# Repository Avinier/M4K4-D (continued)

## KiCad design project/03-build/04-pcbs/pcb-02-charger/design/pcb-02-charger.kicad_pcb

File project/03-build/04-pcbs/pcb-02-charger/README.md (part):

# PCB-02 — Charger, latch and pack sense

> **Superseded by [D-093](../../decisions.md#d-093) (2026-11-06).** Replaced by bought modules: a pushbutton power switch and an INA226/219 voltage/current monitor. The pack is charged outside the robot, so there is no charger. The routed layout below is archived as reference for a later in-robot charger. Nothing here is built or ordered; the folder is kept as the record.

BQ25798 2S charger, on/off latch, pack sense, `ENERGY_OK` and the power-button input `J2-9`.

| | |
|---|---|
| Register | [04-pcbs board register](../README.md#board-register) |
| Project BOM | CH-041 in [BOM.csv](../../BOM.csv) |
| Location | Body, behind the rear panel (vertical) |
| Specification | [charge-path.md §4](../charge-path.md#4-pcb-02--charger-block)<br>[power-boards.md §6](../power-boards.md#6-pcb-02-power-button-input-d-041)<br>[RP-02 board-specs.md](../../../02-prototypes/RP-02-electrical/board-specs.md) (read-only reference)<br>[open items](../open-items.md) CP-OI-02, CP-OI-09, CP-OI-15<br>[D-040](../../decisions.md#d-040), [D-041](../../decisions.md#d-041) |
| CAD placeholder | `power_distribution_boards()` in [`body_v1_model.py`](../../02-body/v1/cad/body_v1_model.py) |
| CAD labels | `PCB02_CHARGE_AND_SYSTEM_POWER` |
| Final CAD | `Custom PCBs › PCB-02 charger, latch and pack sense` in [makad-v1.step.py](../../final/v1/cad/makad-v1.step.py) |

## Stages

See [workflow.md](../workflow.md) for what each stage involves and when it is done.

| Stage | Status | Revision / evidence | Date |
|---|---|---|---|
| 1. Design | In progress | Inputs frozen, frame mount checked (D-083); schematic ERC 0/0; fit-study placement of all 119 footprints at 50 × 36 mm (D-084); routing not started | 2026-11-03 |
| 2. Procure | — | — | — |
| 3. Integrate | — | — | — |

## Inputs

### Lesson 1 — input freeze (2026-11-02)

**Authority order.** The build baseline is [power-boards.md](../power-boards.md) (D-038), with charge-specific changes in [charge-path.md](../charge-path.md) and [D-040](../../decisions.md#d-040), followed by the button deltas in [D-041](../../decisions.md#d-041). The [RP-02 board specification](../../../02-prototypes/RP-02-electrical/board-specs.md) is read-only architecture history; where it differs, the build deltas win. The BOM identity is [CH-041](../../BOM.csv). The remaining gates are [CP-OI-02, CP-OI-06, CP-OI-09 and CP-OI-15](../open-items.md#charge-path-pcb-13-inlet-and-the-pcb-02-charger-d-040-charge-pathmd).

Primary-source cross-checks for this lesson: TI [BQ25798 Rev C datasheet](https://www.ti.com/lit/ds/slusdv2c/slusdv2c.pdf) and [BQ25798EVM user guide](https://www.ti.com/lit/ug/sluucb5c/sluucb5c.pdf); Würth [74437346022 datasheet](https://www.we-online.com/components/products/datasheet/74437346022.pdf). Sourcing pages checked: [LCSC BQ25798RQMR C2876593](https://www.lcsc.com/product-detail/C2876593.html), [element14 India LTC2954 order 4027758](https://in.element14.com/analog-devices/ltc2954its8-2-trpbf/pushbutton-controller-26-4v-tsot/dp/4027758), and [LCSC LTC2954 C580656](https://www.lcsc.com/product-image/C580656.html).

**Fixed electrical boundary.** PCB-13 rev A owns the USB-C receptacle, PD negotiation and input switch. PCB-02 receives only the switched `VSNK` and ground at `J2-8`; the connector pinout and voltage/current envelope below are fixed by [PCB-13's interface freeze](../pcb-13-charge-inlet/README.md#interface-to-pcb-02-fixed-here). `J2-9` is the side-entry GH2 power-button input required by D-041.

| PCB-02 connector / destination | Contract frozen for schematic |
|---|---|
| `J2-8` from PCB-13 | Micro-Fit 3.0 2-way, pin 1 `VSNK`, pin 2 `GND`; normal 9/15 V, blank-STUSB NVM 20 V, 28.35 V surge ceiling; 1.38 A normal maximum and 3 A design current. |
| `J2-1` to pack/fuse-side star | Micro-Fit+ 1×2, pin 1 `BATBUS-C`, pin 2 `PGND` (star). `J2-2` is deleted by D-039; the pack does not connect directly to PCB-02's charger `BAT` sense point. `BATP` returns by a separate 100 Ω Kelvin connection to pin 1. |
| `J2-3` to PCB-04 | Micro-Fit+ 2×2: pin 1 `OPBUS`, pin 2 `CHGBUS`, pin 3 `OPBUS_RTN`, pin 4 `CHGBUS_RTN`. The harness carries operating power and charge-only logic power separately. |
| `J2-4` to PCB-04 | GH10 pin order: 1 GND, 2 `+5V_C2`, 3 `PG_C2`, 4 `PG_BASE`, 5 `SEQ_EN`, 6 `PG_COMPUTE`, 7 `PG_DISPLAY`, 8 `PG_AUDIO`, 9 spare, 10 GND. |
| `J2-5` to PCB-03 | GH8 pin order (D-082): 1 GND, 2 `CHARGE_ABSENT`, 3 `ENERGY_OK`, 4 `SYSTEM_ARM`, 5 `MOTOR_PRESENT`, 6 GND, 7 `PERMIT_OK`, 8 GND. `ENERGY_OK` is active-high/open-drain with a PCB-02 pull-up to switched `+5V_C2`; PCB-03 adds a physical receiver pull-down so an open/unpowered source defaults to motor-inhibit. Pull-up/pull-down values must be co-checked against the receiver's VIH/VIL, leakage and cable margin before the schematic is released. |
| `J2-6` to C2/head sideband | GH8 pin order: 1 `SIG_GND`, 2 `V_PACK_ANA`, 3 `SIG_GND`, 4 `STAT`, 5 `INT_PB`, 6 `KILL`, 7 `CHG_ABSENT_3V3`, 8 `ARM_REQ` (D-082). |
| `J2-7` to pack NTC | GH2: both 103AT-2 leads return to PCB-02; one lead is `TS`, the other BQ25798 ground-pad return. Do not return through a cell or `B−` path behind the pack protector. |
| `J2-9` to rear power button | Side-entry JST GH2 (SM02B-GHS-TB), pin 1 `PB_SW`, pin 2 signal `GND`; plug exits +Y, centred Z 88.6. Board includes the 10 kΩ VIN-to-`PB_SW` wetting resistor, the 5.1 kΩ / 0.1 µF `PB` network, and `INT` resets `SYSTEM_ARM`. The button is the power latch input and hardware motor-stop request; there is no E-stop. |

These orders are a board contract, not a layout proposal. Carry the exact 05-harness pin maps into the schematic, preserve separation between `OPBUS` and `CHGBUS`, and name the grounds according to their power/logic roles.

### Lesson 2 — circuit, from first principles (2026-11-02)

A PCB power board is easier to reason about as separate energy paths with explicit gates. A node name is a contract: `BATBUS` is pack energy at the fuse-side star, `OPBUS` is pack energy after the user-controlled operating switch, `VSNK` is adapter energy after PCB-13 has negotiated and switched it, and `SYS` is the BQ25798's system output. They may sit at similar voltages, but they are not interchangeable nets.

```text
USB-C adapter → PCB-13 PD + input FET → VSNK → BQ25798 → BAT / BATP → fused pack entry
                                                    └→ SYS → adapter-enabled gate → CHGBUS → PCB-04
pack → fuse-side star → BATBUS → Q_OP (LTC2954 latch) → OPBUS → PCB-04
                                             └──────────────→ sense + ENERGY_OK
VSNK → charge-present hardware → CHARGE_ABSENT / Q_dis / Q_kill
J2-9 button → LTC2954 PB; LTC2954 INT → clear SYSTEM_ARM and request C2 shutdown
```

The BQ25798 has an internal battery-to-`SYS` path, so `SYS` can be live from the pack even when no adapter is attached. The charge-only gate keeps that battery-backed node from energizing `CHGBUS` in `OFF` or `OPERATE`. PCB-02 sends `OPBUS` and `CHGBUS` as separate power/return pairs to PCB-04; the destination's reverse-blocking source paths keep charge-only power from back-feeding `OPBUS`. This is what permits C2 and the display to run from the adapter during `CHARGE` while the robot's operating bus remains off.

The operating path is separate. The LTC2954 remembers the momentary button state and drives the gate of `Q_OP`, a P-channel FET from `BATBUS` to `OPBUS`. The series permit chain on PCB-03 decides whether motor energy may pass; PCB-02 supplies the independent `CHARGE_ABSENT`, `ENERGY_OK`, and `SYSTEM_ARM` terms. A valid adapter immediately withdraws the charge-absent term so motor permission opens. `Q_kill` pulls LTC2954 `KILL` low and commands `Q_OP` off promptly, including during a button press in `CHARGE`. The roughly 3 s `Q_dis` hard block is a redundant path still to be captured and tested; it is not a three-second permission to keep `OPBUS` live.

The charger is a third path. `VSNK` feeds the BQ25798's `VBUS` and, by strap, both `VAC` pins. The device's internal switching bridge and the external 2.2 µH inductor move energy into the `BAT`/`SYS` outputs. `PROG` sets 2S, 1 A and 750 kHz without firmware; `ILIM_HIZ` limits input draw; the cell NTC at `TS` gates charging by temperature. `BATP` is a separate high-impedance sense connection returned through 100 Ω to the same fuse-side pack-entry point as `BAT`, so charge current through the fuse, harness and protector does not appear as a false pack-voltage change.

| State | Charger / `SYS` | Operating path | Logic and motor result |
|---|---|---|---|
| `OFF` | BQ25798 remains in low-current battery-only mode; `SYS` may be battery-live | LTC2954 is off; `Q_OP` leaves `OPBUS` open | `Q_sys` is open, so no C2/display logic rail; PCB-03 permit chain is inactive |
| `OPERATE` | Charger remains autonomous; no adapter input | Button latch closes `Q_OP`; `OPBUS` feeds operating loads | Logic runs from `OPBUS`; motors still require every PCB-03 permit term |
| `CHARGE` | `VSNK` powers the BQ25798; gated `SYS` is sent on `CHGBUS` | Charge-present path withdraws `CHARGE_ABSENT`; `Q_kill` commands `Q_OP` off promptly; delayed `Q_dis` is the backup hard block | C2/display run for indication; a button press cannot latch `OPERATE`; motors are inhibited |

The button press has two time scales. In `OPERATE`, LTC2954 `INT` drops after about 32 ms, so hardware clears `SYSTEM_ARM` and removes motor permission without waiting for firmware. C2 starts its orderly shutdown only after the press stays low for 1 s. Holding about 5.2 s invokes the latch's hardware force-off if C2 is hung. `R_WET` raises pressed-contact current from the LTC2954's internal-pull-up 19 µA to about 0.84 mA; the open switch consumes no `R_WET` current when released. This is a power button with a safety-stop function; there is no E-stop in this build.

**Lesson 2 decisions.** The read-only RP-02 `board-specs.md` has two `SYS`-gate descriptions: §4.1 shows a gated P-FET plus Schottky OR with `OPBUS`, while §6.3 describes a `TPS22810` gate to the separate `C2B`/`DISB` inputs and PCB-04 reverse-blocking e-fuses. The fixed harness sends separate `OPBUS` and `CHGBUS` rails. Use separate `OPBUS` and adapter-gated `CHGBUS`, leaving source ORing at PCB-04 as §6.3 describes. Carry 5.7 V falling / 6.4 V rising as provisional `ENERGY_OK` values, with the EN-02/03 calculation and bench validation as release gates.

Second, the RP-02 board-spec proposal is 5.7 V falling (5.53–5.87 V), 6.4 V rising, 1 ms falling qualification and at least 100 ms clear dwell, sensed on loaded `OPBUS`. `power-boards.md` carries the 5.7 V value forward. But the registered [brownout/reset contract](../../../02-prototypes/RP-02-electrical/brownout-restart-contract.md) says numeric thresholds remain evidence-gated and lists the pack, converter, path-resistance, stop-load, monitor-accuracy and reaction-time inputs that must be bound before a threshold is valid. Therefore 5.7/6.4 V is a candidate circuit target, not a released safety setting. The comparator topology and exact IC are also open; the board spec calls only for a local C2-branch 3.3 V supply, nano-power comparator and open-drain output.

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
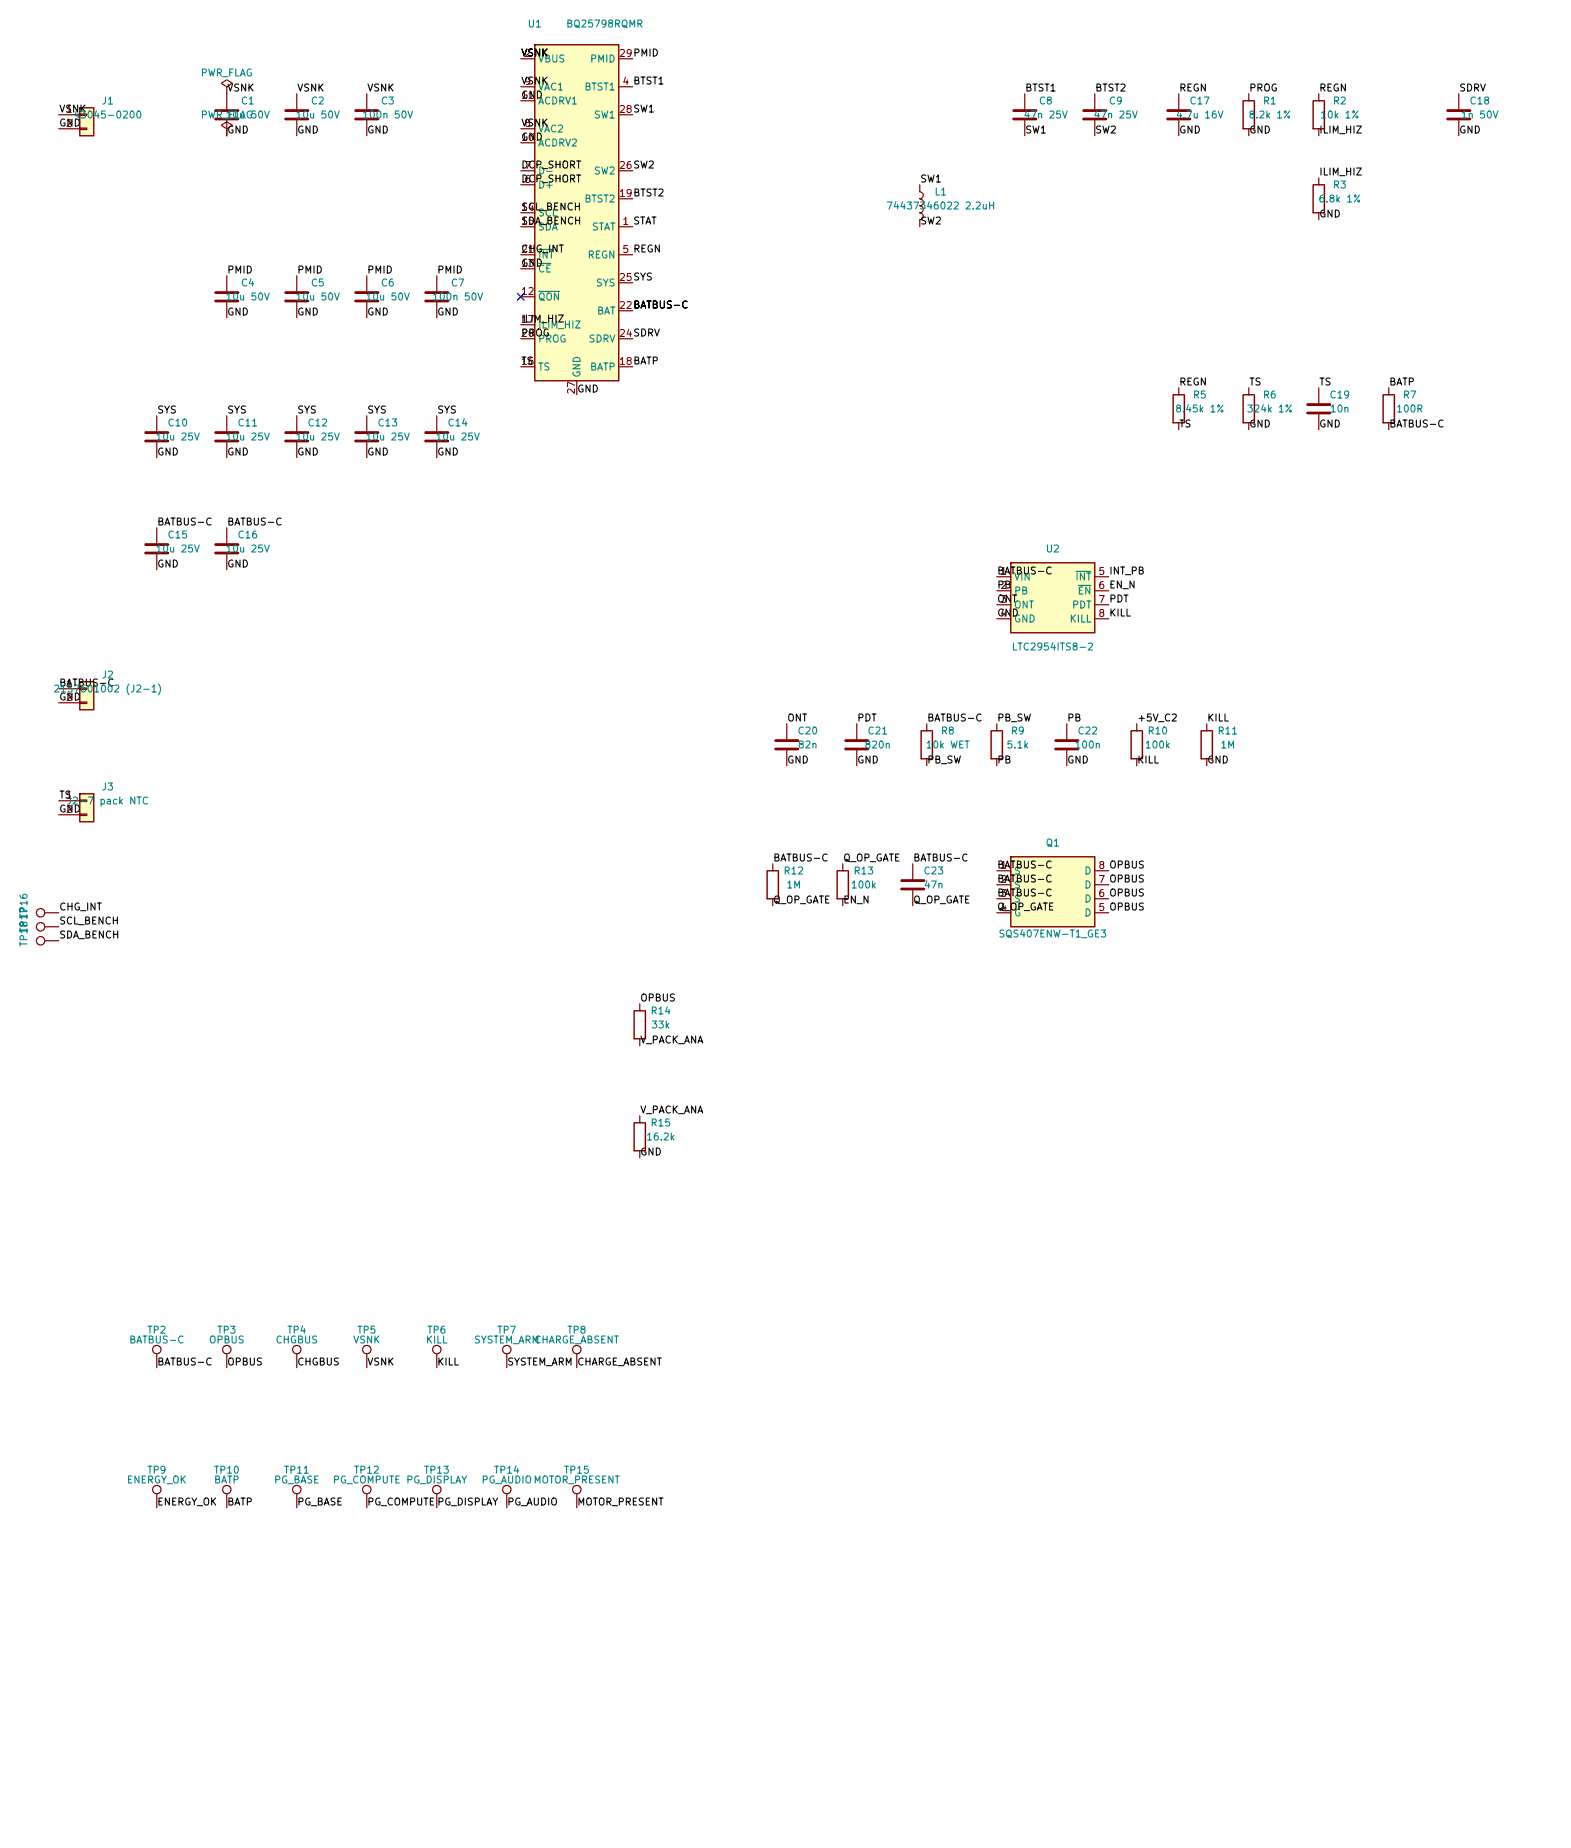
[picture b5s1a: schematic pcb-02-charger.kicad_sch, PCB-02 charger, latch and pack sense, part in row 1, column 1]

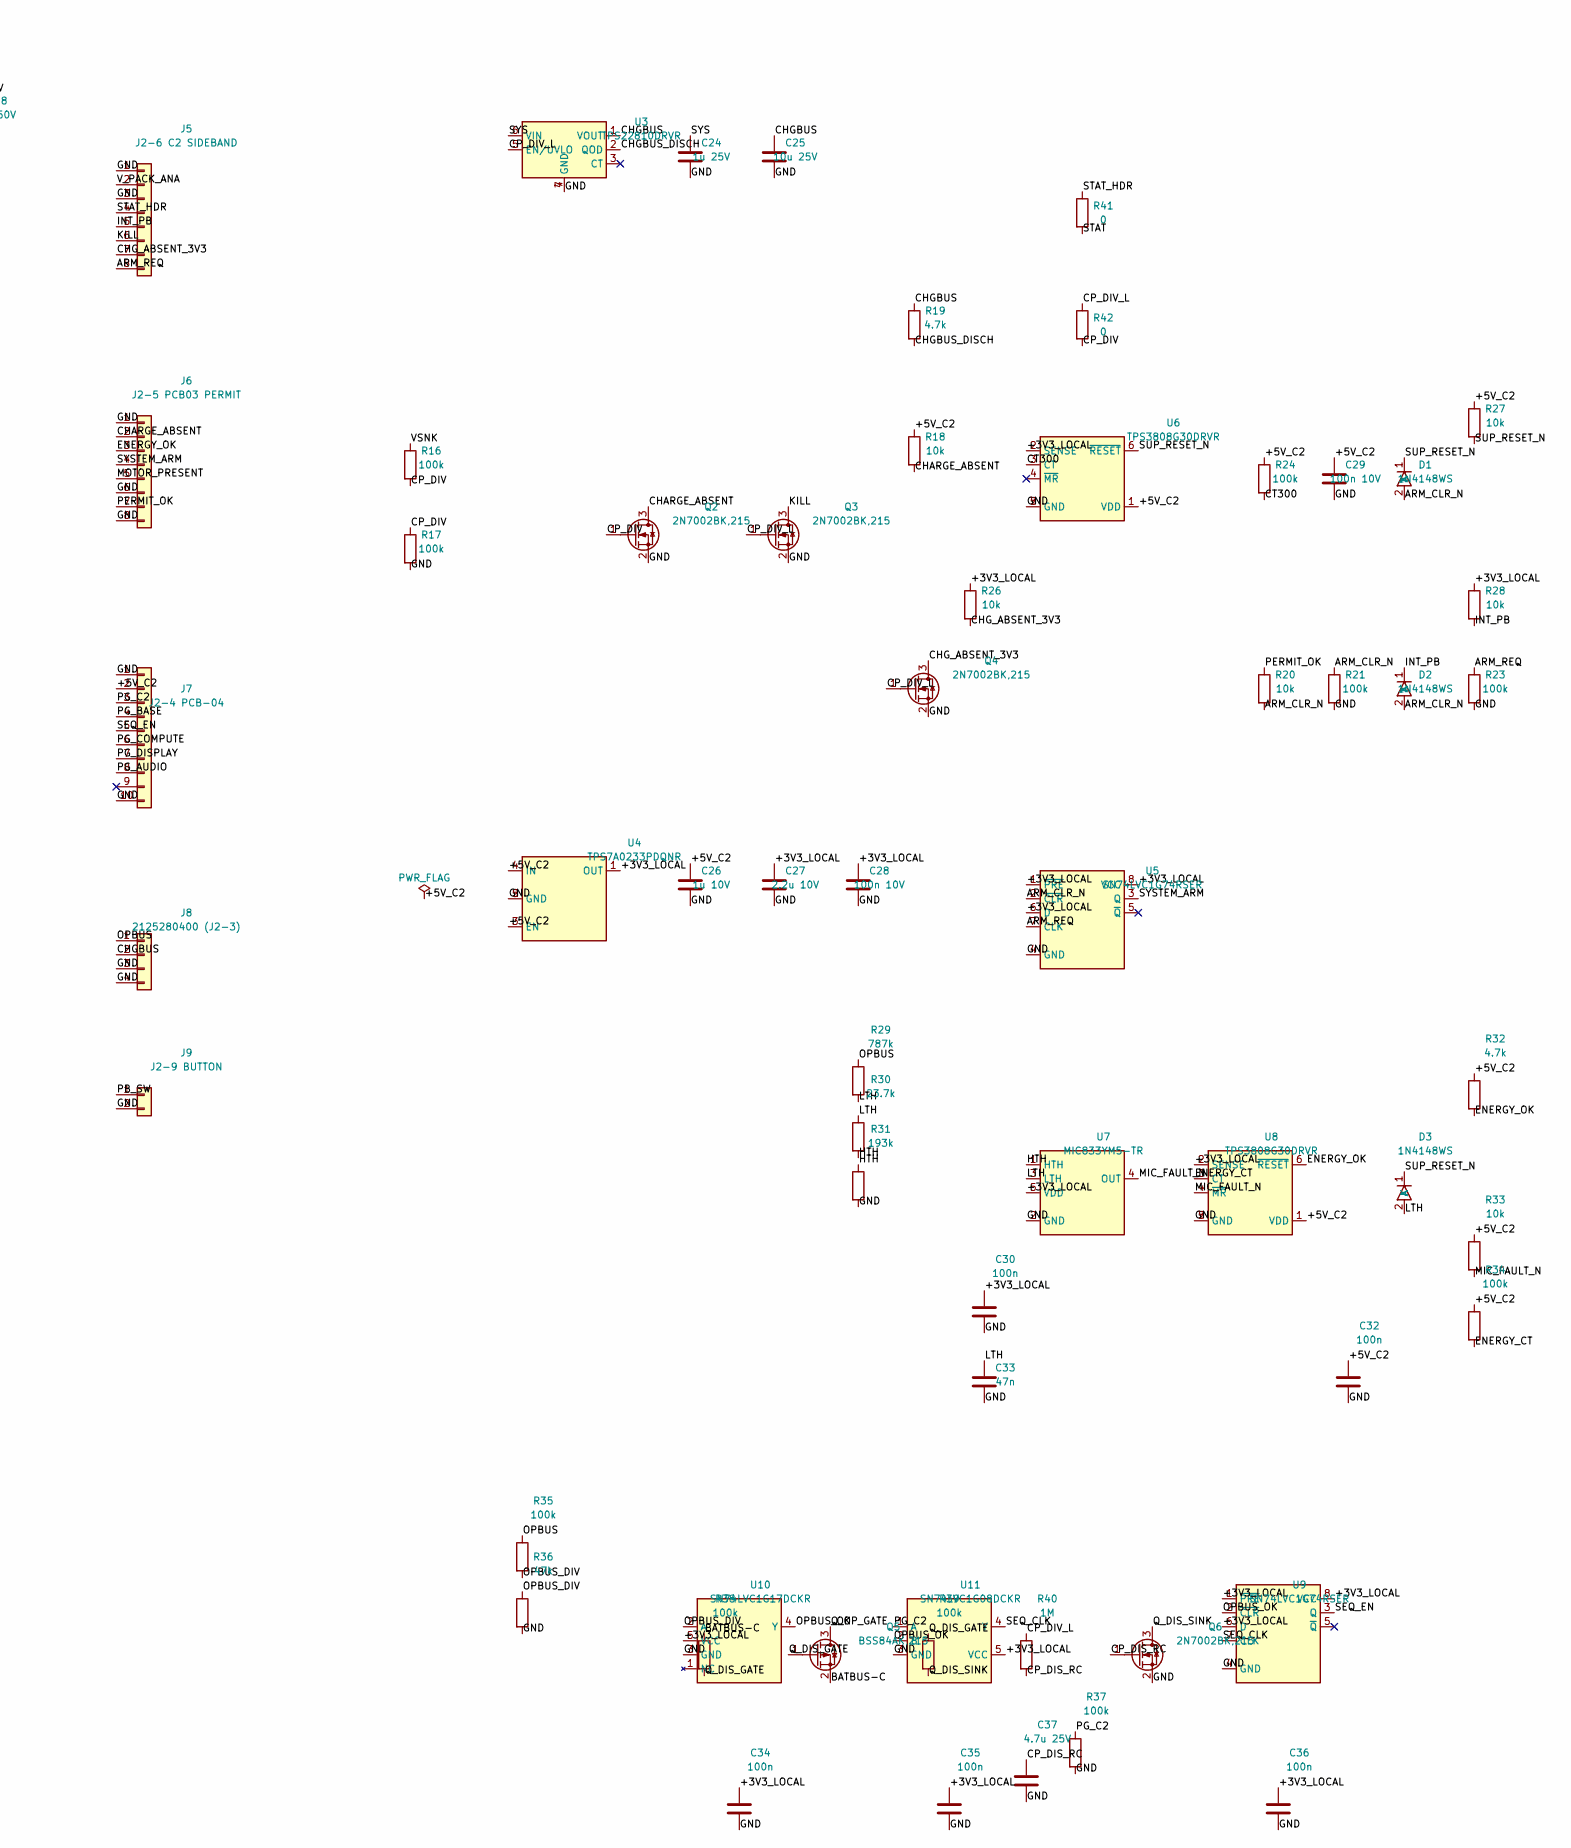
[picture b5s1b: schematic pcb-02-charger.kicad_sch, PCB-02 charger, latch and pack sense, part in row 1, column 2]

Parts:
C1, C2, C4, C5, C6: 10u 50V; C_1206_3216Metric
C3, C7: 100n 50V; C_0402_1005Metric
C8, C9: 47n 25V; C_0402_1005Metric
C10, C11, C12, C13, C14, C15, C16, C25: 10u 25V; C_1206_3216Metric
C17: 4.7u 16V; C_0603_1608Metric
C18: 1n 50V; C_0402_1005Metric
C19: 10n; C_0402_1005Metric
C20: 82n; C_0402_1005Metric
C21: 820n; C_0603_1608Metric
C22, C30, C32, C34, C35, C36: 100n; C_0402_1005Metric
C23, C33: 47n; C_0402_1005Metric
C24: 1u 25V; C_0603_1608Metric
C26: 1u 10V; C_0603_1608Metric
C27: 2.2u 10V; C_0603_1608Metric
C28, C29: 100n 10V; C_0402_1005Metric
C37: 4.7u 25V; C_1206_3216Metric
D1, D2, D3: 1N4148WS; D_SOD-323
J1: 43045-0200; Molex_Micro-Fit_3.0_43045-0200_2x01_P3.00mm_Horizontal
J2: 2157601002 (J2-1); Molex_MicroFitPlus_2157601002
J3: J2-7 pack NTC; JST_GH_BM02B-GHS-TBT_1x02-1MP_P1.25mm_Vertical
J5: J2-6 C2 SIDEBAND; JST_GH_BM08B-GHS-TBT_1x08-1MP_P1.25mm_Vertical
J6: J2-5 PCB03 PERMIT; JST_GH_BM08B-GHS-TBT_1x08-1MP_P1.25mm_Vertical
J7: J2-4 PCB-04; JST_GH_BM10B-GHS-TBT_1x10-1MP_P1.25mm_Vertical
J8: 2125280400 (J2-3); Molex_MicroFitPlus_2125280400
J9: J2-9 BUTTON; JST_GH_SM02B-GHS-TB_1x02-1MP_P1.25mm_Horizontal
L1: 74437346022 2.2uH; Wuerth_74437346022
Q1: SQS407ENW-T1_GE3; Vishay_PowerPAK_1212-8_Single_D5678
Q2, Q3, Q4, Q6: 2N7002BK,215; SOT-23
Q5: BSS84AK,215; SOT-23
R1: 8.2k 1%; R_0402_1005Metric
R2: 10k 1%; R_0402_1005Metric
R3: 6.8k 1%; R_0402_1005Metric
R5: 8.45k 1%; R_0402_1005Metric
R6: 324k 1%; R_0402_1005Metric
R7: 100R; R_0402_1005Metric
R8: 10k WET; R_0402_1005Metric
R9: 5.1k; R_0402_1005Metric
R10, R13, R16, R17, R21, R23, R24, R34, R35, R37, R38, R39: 100k; R_0402_1005Metric
R11, R12, R40: 1M; R_0402_1005Metric
R14: 33k; R_0402_1005Metric
R15: 16.2k; R_0402_1005Metric
R18, R20, R26, R27, R28, R33: 10k; R_0402_1005Metric
R19, R32: 4.7k; R_0402_1005Metric
R29: 787k; R_0402_1005Metric
R30: 23.7k; R_0402_1005Metric
R31: 193k; R_0402_1005Metric
R36: 47k; R_0402_1005Metric
R41, R42: 0; R_0402_1005Metric
TP2: BATBUS-C; TestPoint_Pad_D1.0mm
TP3: OPBUS; TestPoint_Pad_D1.0mm
TP4: CHGBUS; TestPoint_Pad_D1.0mm
TP5: VSNK; TestPoint_Pad_D1.0mm
TP6: KILL; TestPoint_Pad_D1.0mm
TP7: SYSTEM_ARM; TestPoint_Pad_D1.0mm
TP8: CHARGE_ABSENT; TestPoint_Pad_D1.0mm
TP9: ENERGY_OK; TestPoint_Pad_D1.0mm
TP10: BATP; TestPoint_Pad_D1.0mm
TP11: PG_BASE; TestPoint_Pad_D1.0mm
TP12: PG_COMPUTE; TestPoint_Pad_D1.0mm
TP13: PG_DISPLAY; TestPoint_Pad_D1.0mm
TP14: PG_AUDIO; TestPoint_Pad_D1.0mm
TP15: MOTOR_PRESENT; TestPoint_Pad_D1.0mm
TP16: CHG_INT; TestPoint_Pad_D1.0mm
TP17: SCL_BENCH; TestPoint_Pad_D1.0mm
TP18: SDA_BENCH; TestPoint_Pad_D1.0mm
U1: BQ25798RQMR; Texas_RQM0029A_VQFN-29_4x4mm_P0.4mm; MPN BQ25798RQMR
U2: LTC2954ITS8-2; TSOT-23-8_LTC_TS8
U3: TPS22810DRVR; WSON-6-1EP_2x2mm_P0.65mm_EP1x1.6mm
U4: TPS7A0233PDQNR; Texas_X2SON-4_1x1mm_P0.65mm_EP0.48
U5, U9: SN74LVC1G74RSER; Texas_UQFN-8_1.5x1.5mm_P0.5mm
U6, U8: TPS3808G30DRVR; WSON-6-1EP_2x2mm_P0.65mm_EP1x1.6mm
U7: MIC833YM5-TR; SOT-23-5
U10: SN74LVC1G17DCKR; SOT-353_SC-70-5
U11: SN74LVC1G08DCKR; SOT-353_SC-70-5

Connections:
/+3V3_LOCAL: C27.1, C28.1, C30.1, C34.1, C35.1, C36.1, R26.1, R28.1, U4.1 (OUT), U5.1 (~PRE), U5.6 (D), U5.8 (VCC), U6.2 (SENSE), U7.5 (VDD), U8.2 (SENSE), U9.1 (~PRE), U9.6 (D), U9.8 (VCC), U10.5 (VCC), U11.5 (VCC)
/+5V_C2: C26.1, C29.1, C32.1, J7.2, R10.1, R18.1, R24.1, R27.1, R32.1, R33.1, R34.1, U4.3 (EN), U4.4 (IN), U6.1 (VDD), U8.1 (VDD)
/ARM_CLR_N: D1.2 (A), D2.2 (A), R20.2, R21.1, U5.2 (~CLR)
/ARM_REQ: J5.8, R23.1, U5.7 (CLK)
/BATBUS-C: C15.1, C16.1, C23.1, J2.1, Q1.1 (S), Q1.2 (S), Q1.3 (S), Q5.2 (S), R7.2, R8.1, R12.1, R38.1, TP2.1 (1_1), U1.22 (BAT), U1.23 (BAT), U2.1 (VIN)
/BATP: R7.1, TP10.1 (1_1), U1.18 (BATP)
/BTST1: C8.1, U1.4 (BTST1)
/BTST2: C9.1, U1.19 (BTST2)
/CHARGE_ABSENT: J6.2, Q2.3 (D), R18.2, TP8.1 (1_1)
/CHGBUS: C25.1, J8.2, R19.1, TP4.1 (1_1), U3.1 (VOUT)
/CHGBUS_DISCH: R19.2, U3.2 (QOD)
/CHG_ABSENT_3V3: J5.7, Q4.3 (D), R26.2
/CHG_INT: TP16.1 (1_1), U1.21 (~INT)
/CP_DIS_RC: C37.1, Q6.1 (G), R40.2
/CP_DIV: Q2.1 (G), R16.2, R17.1, R42.2
/CP_DIV_L: Q3.1 (G), Q4.1 (G), R40.1, R42.1, U3.5 (EN/UVLO)
/CT300: R24.2, U6.3 (CT)
/DCP_SHORT: U1.6 (D+), U1.7 (D-)
/ENERGY_CT: R34.2, U8.3 (CT)
/ENERGY_OK: J6.3, R32.2, TP9.1 (1_1), U8.6 (~RESET)
/EN_N: R13.2, U2.6 (~EN)
/GND: C1.2, C2.2, C3.2, C4.2, C5.2, C6.2, C7.2, C10.2, C11.2, C12.2, C13.2, C14.2, C15.2, C16.2, C17.2, C18.2, C19.2, C20.2, C21.2, C22.2, C24.2, C25.2, C26.2, C27.2, C28.2, C29.2, C30.2, C32.2, C33.2, C34.2, C35.2, C36.2, C37.2, J1.2, J2.2, J3.2, J5.1, J5.3, J6.1, J6.6, J6.8, J7.1, J7.10, J8.3, J8.4, J9.2, Q2.2 (S), Q3.2 (S), Q4.2 (S), Q6.2 (S), R1.2, R3.2, R6.2, R11.2, R15.2, R17.2, R21.2, R23.2, R31.2, R36.2, R37.2, U1.10 (ACDRV2), U1.11 (ACDRV1), U1.13 (~CE), U1.27 (GND), U2.4 (GND), U3.4 (GND), U3.7 (GND), U4.2 (GND), U4.5 (GND), U5.4 (GND), U6.5 (GND), U6.7 (GND), U7.2 (GND), U8.5 (GND), U8.7 (GND), U9.4 (GND), U10.3 (GND), U11.3 (GND)
/HTH: R30.2, R31.1, U7.1 (HTH)
/ILIM_HIZ: R2.2, R3.1, U1.17 (ILIM_HIZ)
/INT_PB: D2.1 (K), J5.5, R28.2, U2.5 (~INT)
/KILL: J5.6, Q3.3 (D), R10.2, R11.1, TP6.1 (1_1), U2.8 (KILL)
/LTH: C33.1, D3.2 (A), R29.2, R30.1, U7.3 (LTH)
/MIC_FAULT_N: R33.2, U7.4 (OUT), U8.4 (~MR)
/MOTOR_PRESENT: J6.5, TP15.1 (1_1)
/ONT: C20.1, U2.3 (ONT)
/OPBUS: J8.1, Q1.5 (D), Q1.6 (D), Q1.7 (D), Q1.8 (D), R14.1, R29.1, R35.1, TP3.1 (1_1)
/OPBUS_DIV: R35.2, R36.1, U10.2 (A)
/OPBUS_OK: U9.2 (~CLR), U10.4 (Y), U11.2 (B)
/PB: C22.1, R9.2, U2.2 (PB)
/PB_SW: J9.1, R8.2, R9.1
/PDT: C21.1, U2.7 (PDT)
/PERMIT_OK: J6.7, R20.1
/PG_AUDIO: J7.8, TP14.1 (1_1)
/PG_BASE: J7.4, TP11.1 (1_1)
/PG_C2: J7.3, R37.1, U11.1 (A)
/PG_COMPUTE: J7.6, TP12.1 (1_1)
/PG_DISPLAY: J7.7, TP13.1 (1_1)
/PMID: C4.1, C5.1, C6.1, C7.1, U1.29 (PMID)
/PROG: R1.1, U1.20 (PROG)
/Q_DIS_GATE: Q5.1 (G), R38.2, R39.1
/Q_DIS_SINK: Q6.3 (D), R39.2
/Q_OP_GATE: C23.2, Q1.4 (G), Q5.3 (D), R12.2, R13.1
/REGN: C17.1, R2.1, R5.1, U1.5 (REGN)
/SCL_BENCH: TP17.1 (1_1), U1.14 (SCL)
/SDA_BENCH: TP18.1 (1_1), U1.15 (SDA)
/SDRV: C18.1, U1.24 (SDRV)
/SEQ_CLK: U9.7 (CLK), U11.4 (Y)
/SEQ_EN: J7.5, U9.3 (Q)
/STAT: R41.2, U1.1 (STAT)
/STAT_HDR: J5.4, R41.1
/SUP_RESET_N: D1.1 (K), D3.1 (K), R27.2, U6.6 (~RESET)
/SW1: C8.2, L1.1, U1.28 (SW1)
/SW2: C9.2, L1.2, U1.26 (SW2)
/SYS: C10.1, C11.1, C12.1, C13.1, C14.1, C24.1, U1.25 (SYS), U3.6 (VIN)
/SYSTEM_ARM: J6.4, TP7.1 (1_1), U5.3 (Q)
/TS: C19.1, J3.1, R5.2, R6.1, U1.16 (TS)
/VSNK: C1.1, C2.1, C3.1, J1.1, R16.1, TP5.1 (1_1), U1.2 (VBUS), U1.3 (VBUS), U1.8 (VAC2), U1.9 (VAC1)
/V_PACK_ANA: J5.2, R14.2, R15.1

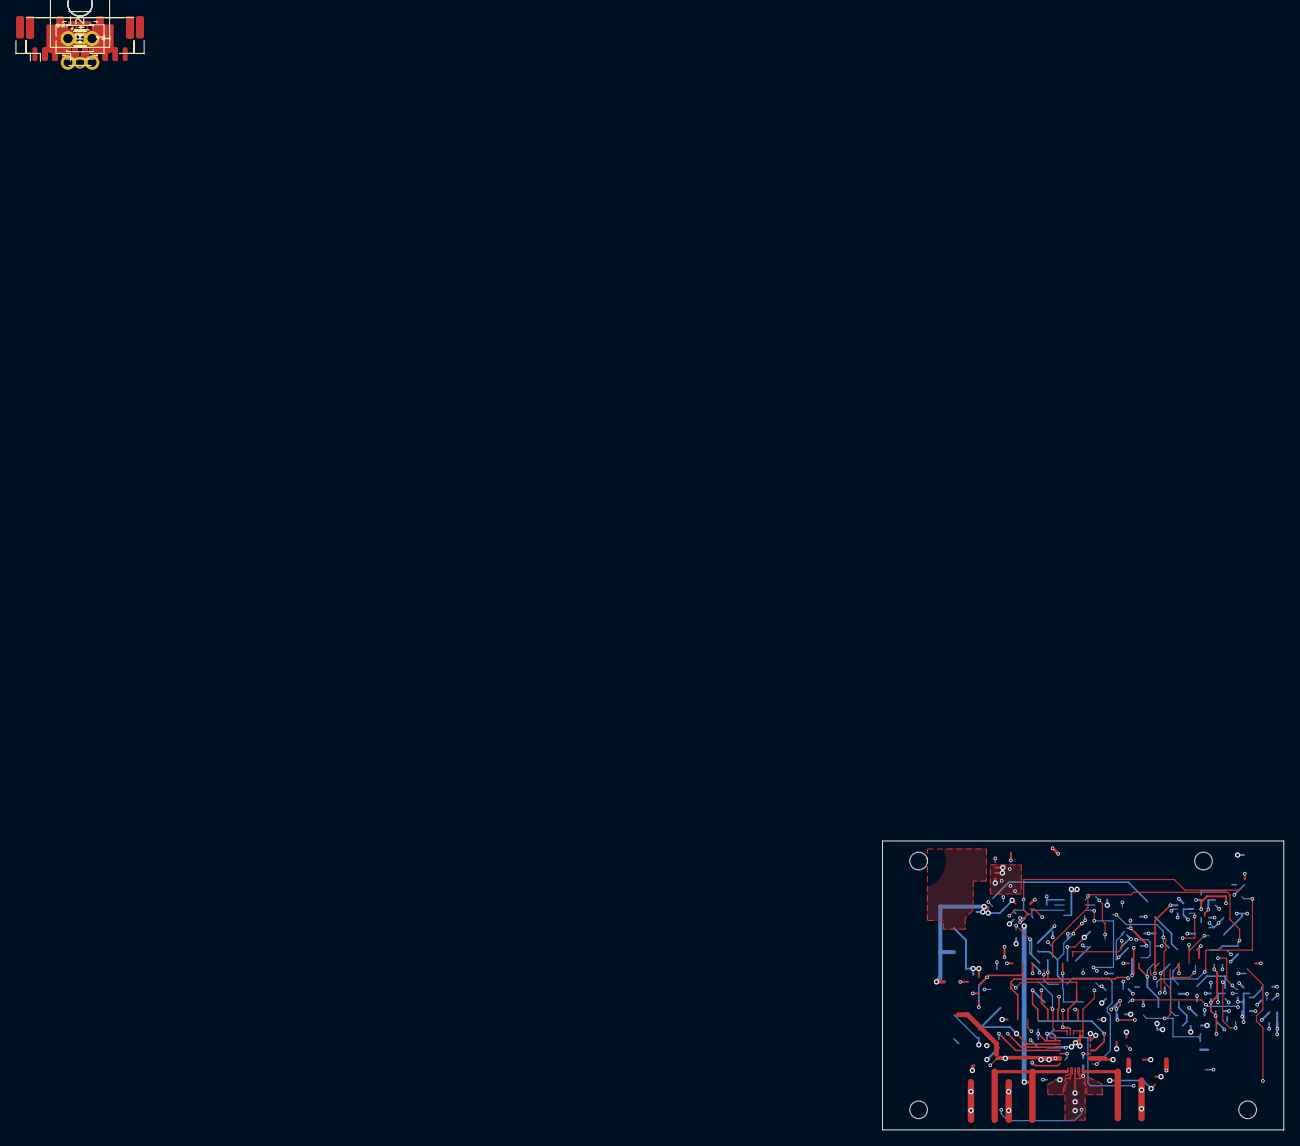
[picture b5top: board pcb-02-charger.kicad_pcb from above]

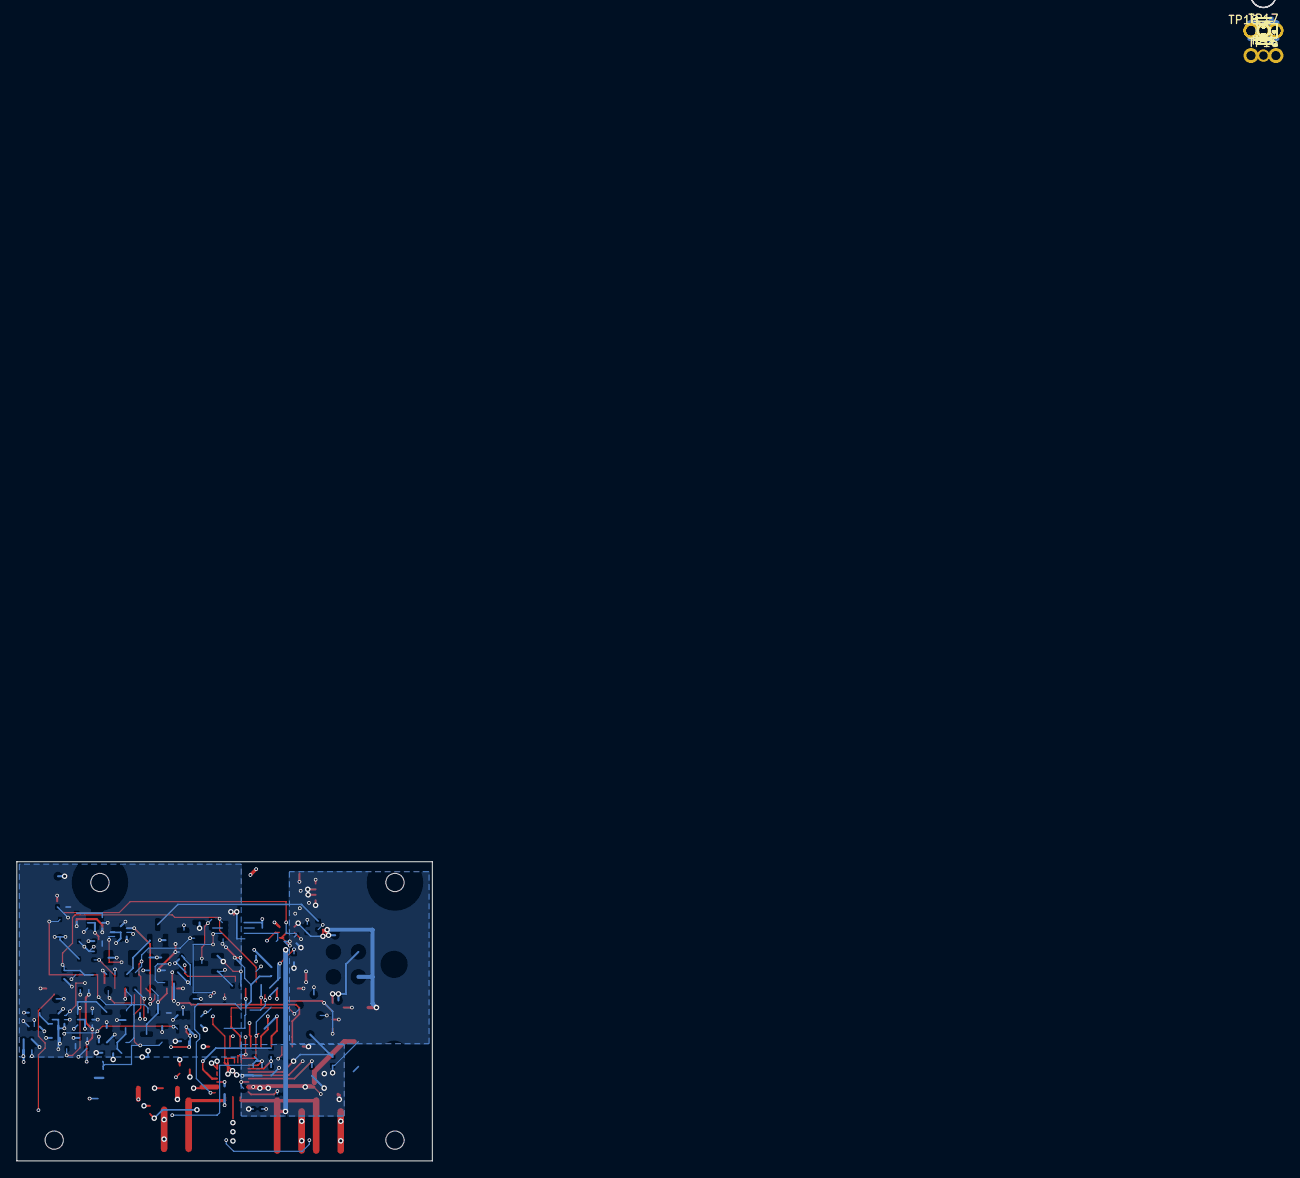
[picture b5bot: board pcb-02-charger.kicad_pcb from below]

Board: 4 copper layers, 50.0 x 36.0 mm, 121 parts (87 on the bottom side), 63 nets.

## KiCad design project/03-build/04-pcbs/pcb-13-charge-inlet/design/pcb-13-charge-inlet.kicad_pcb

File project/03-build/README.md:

# 03 — Build

Turn the [prototype decisions](../02-prototypes/) into parts that can be printed, assembled, measured, and revised. This phase is complete when the built robot passes its integration tests, not when the CAD looks finished.

## Status (2026-11-12)

The build follows the [D-093](decisions.md#d-093) simplification: bought power modules replace the charger, motor-gate, converter, audio, mic and IMU boards. Progress by level is in the [simplification plan §7](simplification-plan.md#7-levels-of-work).

- **Modules** selected ([D-094](decisions.md#d-094), [module-selection.md](module-selection.md)) and **ordered 2026-11-08**; each still has a bench gate (N1–N12).
- **Droid CAD** for the modules, ports and mounts is done ([D-095](decisions.md#d-095)); the chassis front module and the D-095 mount prints are re-exported to [04-print](../04-print/01-chassis/README.md) ([D-099](decisions.md#d-099)).
- **Harness** topology is documented, but [05-harness](05-harness/README.md) is on **electrical HOLD** ([D-096](decisions.md#d-096)): the ~16 A low-pack coincident load exceeds the contact and shunt allowances. Do not cut wire or build the charge/power path yet.
- **Custom boards** ([04-pcbs](04-pcbs/README.md)): PCB-09 rev B routed; PCB-08, PCB-12, PCB-14 and PCB-16 are rev A drafts (do not order). The head wiring route is set by [D-104](decisions.md#d-104) (hollow −Y trunnion) and [D-105](decisions.md#d-105) (camera ribbon loop).
- **BOM**: [BOM.csv](BOM.csv) is reconciled to D-093–D-097; the subsystem BOM snapshots still predate D-093.

## Where things are

| Record | Holds |
|---|---|
| [decisions.md](decisions.md) | The ledger: every decision, part selection, BOM change and CAD edit |
| [BOM.csv](BOM.csv) | The single parts register |
| [BOM-deliveries.md](BOM-deliveries.md) | What has physically arrived, mapped to BOM rows, with problems found |
| [TODO.md](TODO.md) | Open ordering, receiving and release actions |
| [simplification-plan.md](simplification-plan.md) | The D-093 change map, levels of work and bench register (N-tests) |
| [module-selection.md](module-selection.md) | Bought modules (M1–M13) and their acceptance gates |
| [01-chassis](01-chassis/), [02-body](02-body/), [03-head](03-head/) | Subsystem specs, BOM snapshots and subsystem-only CAD |
| [04-pcbs](04-pcbs/README.md) | Custom board register, design workflow and playbook |
| [04-software](04-software/firmware-requirements.md) | Firmware requirements (low-battery stop, button-off, servo limits, mics) |
| [05-harness](05-harness/README.md) | Connectors, cables, pinouts and service breaks |
| [final/v1](final/v1/README.md) | The whole-robot CAD and its checks, plus the [print guide](final/v1/printguide.md) |

Printing (lab, workflow, coupons, per-part print settings) is in [04-print](../04-print/README.md).

## Governing context

**From 2026-09-28, `03-build/` governs.** Record every new decision, part selection, BOM change and CAD edit here, in the subsystem and version folder it belongs to, and log it in [`decisions.md`](decisions.md).

[`02-prototypes/`](../02-prototypes/) and its RP folders, including RP-03 locomotion and RP-06 CAD, are **read-only reference**. Link to them for earlier research, gates and evidence; do not add decisions to them or edit their CAD. Where an RP document disagrees with `03-build/`, `03-build/` wins.

Each subsystem's `cad/` holds only that subsystem. The whole robot is in [`final/v1/cad/`](final/v1/README.md), and droid-level changes (envelope fixes, cuts, bought-part STEPs) go there with a targeted check.

## BOM conventions

[BOM.csv](BOM.csv) is the single parts register. Subsystem `BOM.md` files are dated working snapshots, not fabrication releases; refresh them deliberately after a BOM change.

In the register, `DESIGN` means custom geometry exists, `CANDIDATE` means a part or family is proposed, `SELECTED` means the build choice is settled with receiving and physical verification still separate, `OPEN` means the design needs a choice before release, and `HOLD` means do not order or fabricate until its blocker is resolved. `SUPERSEDED` rows are kept for history. `supplier_candidate` is a lead to verify, not a stock claim. Update `procurement` and `received_measurements` with order and caliper evidence; do not infer receipt from CAD or an old availability check.

## Build order

1. [Chassis and locomotion](01-chassis/): wheels, drive, supports and the body mounting interface. Test with representative body and head mass and centre of mass.
2. [Body](02-body/): load-bearing frame, packaging, power and wiring, access, cooling and the head support. Recheck its effect on the chassis.
3. [Head](03-head/): build and test the mechanism on its real body support. Part selection and isolated joint tests can start earlier.
4. [Full droid](final/v1/README.md): assemble the subsystems and rerun whole-robot motion, power, thermal, fault and interaction tests.

Work can overlap. Freeze only the interfaces needed for the next release, and record changes that affect another subsystem. Unreleased custom boards do not block isolated chassis fit or controlled external-supply tests.

## What a version means

`v1`, `v2`, `v3`, and later folders are **build iterations**. Each version aims to produce a **print-ready build release** for its defined scope, followed by a physical build and test. A version is not called production-ready before its printed article passes its tests.

Each release needs only these records:

1. **Scope and interfaces** — parts included, assumed loads and mass, dimensions that other subsystems depend on, and known exclusions.
2. **BOM and procurement** — exact purchased parts, quantities, sources, status, and measured dimensions. Keep one project BOM; capture the version's exact BOM as a release snapshot so subsystem lists cannot silently diverge.
3. **Fabrication package** — source CAD and revision, printable exports, material, printer/process settings, orientation, supports, tolerances, inserts, and assembly instructions. Measure received hardware and correct dependent CAD before releasing custom parts.
4. **Test plan and evidence** — focused stress-test research, expected loads, measurable pass/fail criteria set before scored tests, test setup, results, photos/logs, and failures. Mark unrun tests **OPEN**, not passed.
5. **Exit decision** — `PASS`, `ITERATE`, or `HOLD`, with the evidence and the specific change needed. A failed or improved design becomes the next version; a passing subsystem can move forward while its shared interfaces remain tracked.

For the chassis, test at least fit and retention, loaded stiffness, wheel runout, traction and turning, braking and tipping, support/skid behaviour, motor temperature, and service access. Use representative worst-case body/head ballast until those assemblies exist. Reuse the [RP-03 locomotion gates](../02-prototypes/RP-03-locomotion/gates.md) and [RP-06 open items](../02-prototypes/RP-06-cad/TODO.md) as inputs; register relevant numeric limits and test conditions before scoring a run.

The working loop is **select → order → measure → update CAD → release → print/assemble → test → record → iterate or lock**. `LOCKED` means the built article passed its defined tests and its interfaces are controlled. A CAD check or paper calculation alone does not lock a part.

## Documentation rule

Keep these pages shorter and more decisive than [02-prototypes](../02-prototypes/). Link to existing research instead of copying it. State the current decision, revision, evidence, open risk, and next action; remove abandoned options from the active build instructions. Do not call estimates measurements or let a later CAD edit silently change a released version.

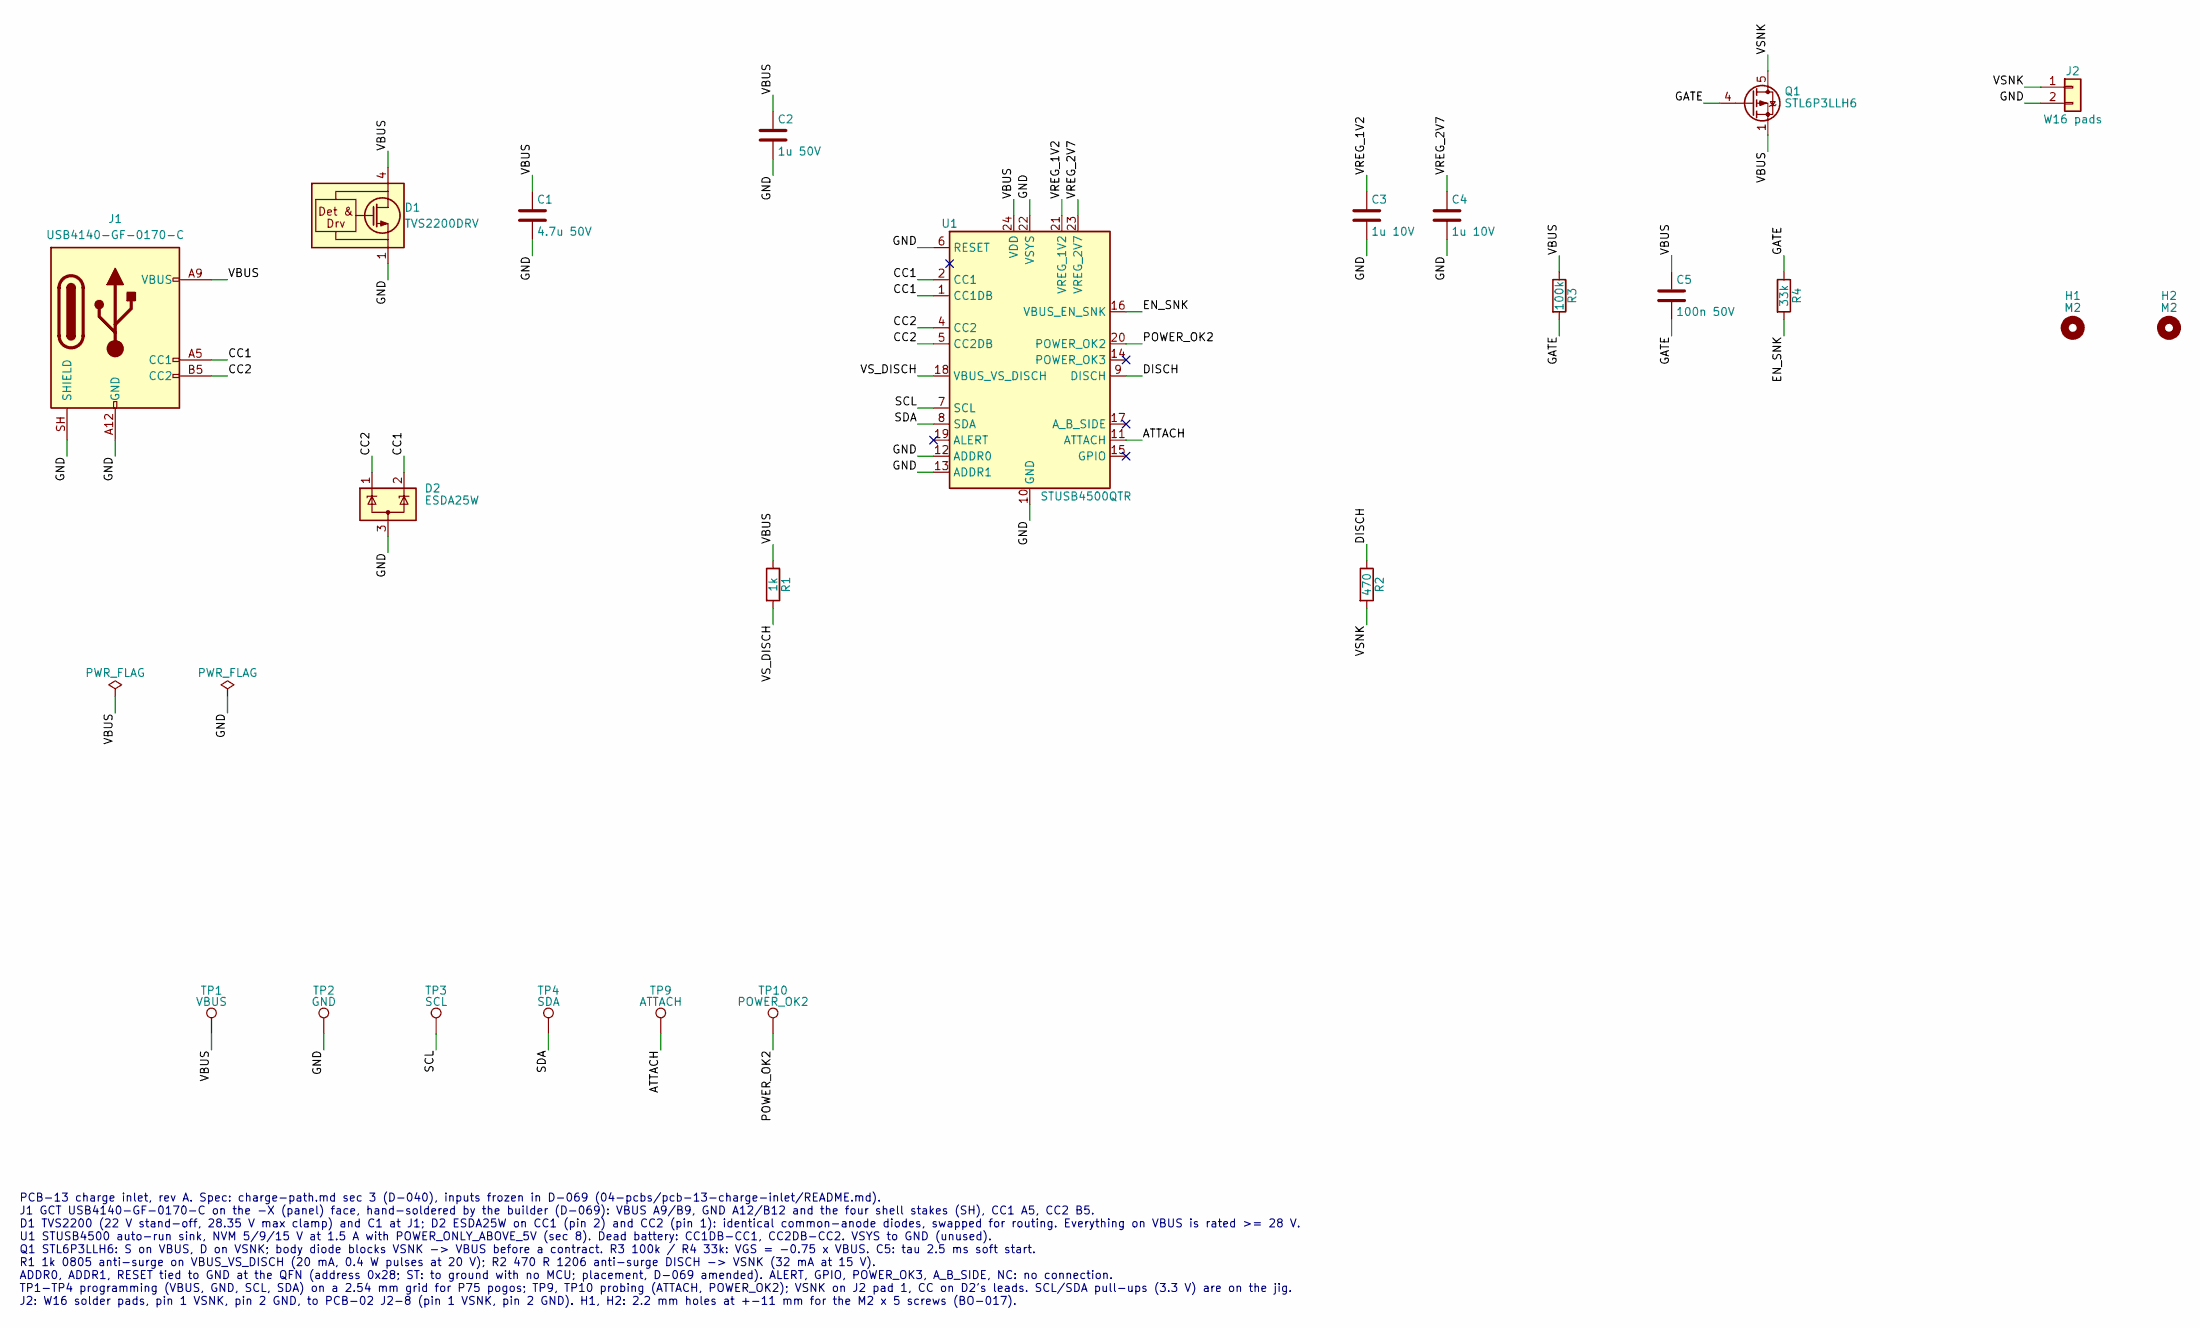
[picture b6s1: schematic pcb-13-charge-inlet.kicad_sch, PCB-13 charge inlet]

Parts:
C1: 4.7u 50V; C_1206_3216Metric; MPN CL31B475KBHNNNE
C2: 1u 50V; C_0603_1608Metric; MPN CL10B105KB8NNNC
C3, C4: 1u 10V; C_0402_1005Metric; MPN CL05A105KP5NNNC
C5: 100n 50V; C_0603_1608Metric; MPN CL10B104KB8NNNC
D1: TVS2200DRV; WSON-6-1EP_2x2mm_P0.65mm_EP1x1.6mm; MPN TVS2200DRVR
D2: ESDA25W; SOT-323_SC-70; MPN ESDA25W
H1, H2: M2; MountingHole_2.2mm_M2
J1: USB4140-GF-0170-C; GCT_USB4140-GF-0170-C; MPN USB4140-GF-0170-C
J2: W16 pads; W16_SolderPads_2x_AWG22
Q1: STL6P3LLH6; ST_PowerFLAT-3.3x3.3_TypeF; MPN STL6P3LLH6
R1: 1k; R_0805_2012Metric; MPN ERJ-P06J102V
R2: 470; R_1206_3216Metric; MPN ERJ-P08J471V
R3: 100k; R_0402_1005Metric
R4: 33k; R_0402_1005Metric
TP1: VBUS; TestPoint_Pad_D1.0mm
TP2: GND; TestPoint_Pad_D1.0mm
TP3: SCL; TestPoint_Pad_D1.0mm
TP4: SDA; TestPoint_Pad_D1.0mm
TP9: ATTACH; TestPoint_Pad_D1.0mm
TP10: POWER_OK2; TestPoint_Pad_D1.0mm
U1: STUSB4500QTR; QFN-24-1EP_4x4mm_P0.5mm_EP2.7x2.7mm; MPN STUSB4500QTR

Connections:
/ATTACH: TP9.1 (1_1), U1.11 (ATTACH)
/CC1: D2.2 (K), J1.A5 (CC1), U1.1 (CC1DB), U1.2 (CC1)
/CC2: D2.1 (K), J1.B5 (CC2), U1.4 (CC2), U1.5 (CC2DB)
/DISCH: R2.1, U1.9 (DISCH)
/EN_SNK: R4.2, U1.16 (VBUS_EN_SNK)
/GATE: C5.2, Q1.4 (G), R3.2, R4.1
/GND: C1.2, C2.2, C3.2, C4.2, D1.1 (GND), D1.2 (GND), D1.3 (GND), D1.7 (GND), D2.3 (A), J1.A12 (GND), J1.B12 (GND), J1.SH (SHIELD), J2.2, TP2.1 (1_1), U1.6 (RESET), U1.10 (GND), U1.12 (ADDR0), U1.13 (ADDR1), U1.22 (VSYS), U1.25 (GND)
/POWER_OK2: TP10.1 (1_1), U1.20 (POWER_OK2)
/SCL: TP3.1 (1_1), U1.7 (SCL)
/SDA: TP4.1 (1_1), U1.8 (SDA)
/VBUS: C1.1, C2.1, C5.1, D1.4 (IN), D1.5 (IN), D1.6 (IN), J1.A9 (VBUS), J1.B9 (VBUS), Q1.1 (S), Q1.2 (S), Q1.3 (S), R1.1, R3.1, TP1.1 (1_1), U1.24 (VDD)
/VREG_1V2: C3.1, U1.21 (VREG_1V2)
/VREG_2V7: C4.1, U1.23 (VREG_2V7)
/VSNK: J2.1, Q1.5 (D), R2.2
/VS_DISCH: R1.2, U1.18 (VBUS_VS_DISCH)

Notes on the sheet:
PCB-13 charge inlet, rev A. Spec: charge-path.md sec 3 (D-040), inputs frozen in D-069 (04-pcbs/pcb-13-charge-inlet/README.md). J1 GCT USB4140-GF-0170-C on the -X (panel) face, hand-soldered by the builder (D-069): VBUS A9/B9, GND A12/B12 and the four shell stakes (SH), CC1 A5, CC2 B5. D1 TVS2200 (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
